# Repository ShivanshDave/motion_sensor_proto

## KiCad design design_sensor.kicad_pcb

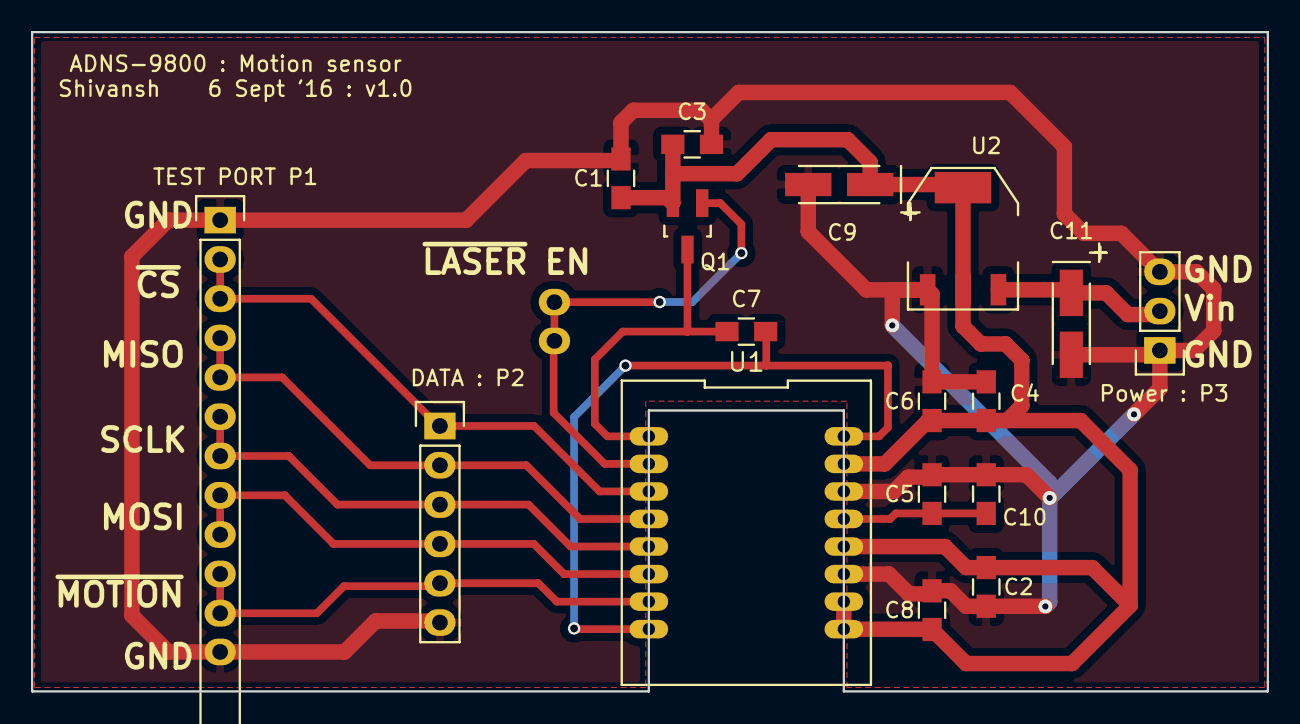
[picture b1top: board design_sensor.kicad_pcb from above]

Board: 2 copper layers, 79.8 x 42.6 mm, 17 parts (0 on the bottom side), 12 nets.

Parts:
C1: 1uF; C_0805_HandSoldering
C2, C3, C4, C10: 0.1uF; C_0805_HandSoldering
C5, C8: 10uF; C_0805_HandSoldering
C6: 3.3uF; C_0805_HandSoldering
C7: 470pF; C_0805_HandSoldering
C9, C11: 10u; TantalC_SizeA_EIA-3216_HandSoldering
DATA : P2: Data; Pin_Header_Straight_1x06
Power : P3: POWER; Pin_Header_Straight_1x03
Q1: Q_PMOS_GSD; SOT-23_Handsoldering
TEST PORT P1: Test Port; Pin_Header_Straight_1x14
U1: ADSN9800; DIP-16_SEPT2_new
U2: LD1117S33CTR; SOT-223

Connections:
/MISO: DATA : P2.2, TEST PORT P1.4, TEST PORT P1.5, U1.4
/MOSI: DATA : P2.4, TEST PORT P1.8, TEST PORT P1.9, U1.6
/SCLK: DATA : P2.3, TEST PORT P1.6, TEST PORT P1.7, U1.5
/VIN: C11.1, Power : P3.2, U2.3
/~CS: DATA : P2.1, TEST PORT P1.2, TEST PORT P1.3, U1.3
/~Laser_EN: Q1.1, TEST PORT P1.12, TEST PORT P1.13, U1.2
/~Motion: DATA : P2.5, TEST PORT P1.10, TEST PORT P1.11, U1.7
GND: C1.2, C2.2, C3.2, C4.2, C5.2, C6.2, C8.2, C9.2, C10.2, C11.2, DATA : P2.6, Power : P3.1, Power : P3.3, TEST PORT P1.1, TEST PORT P1.14, U1.11, U1.14, U2.1
unnamed: C7.1, Q1.3, U1.1
unnamed: C7.2, U1.8, U1.16
unnamed: C5.1, C10.1, U1.13
VDD: C1.1, C2.1, C3.1, C4.1, C6.1, C8.1, C9.1, Q1.2, U1.9, U1.10, U1.12, U1.15, U2.2

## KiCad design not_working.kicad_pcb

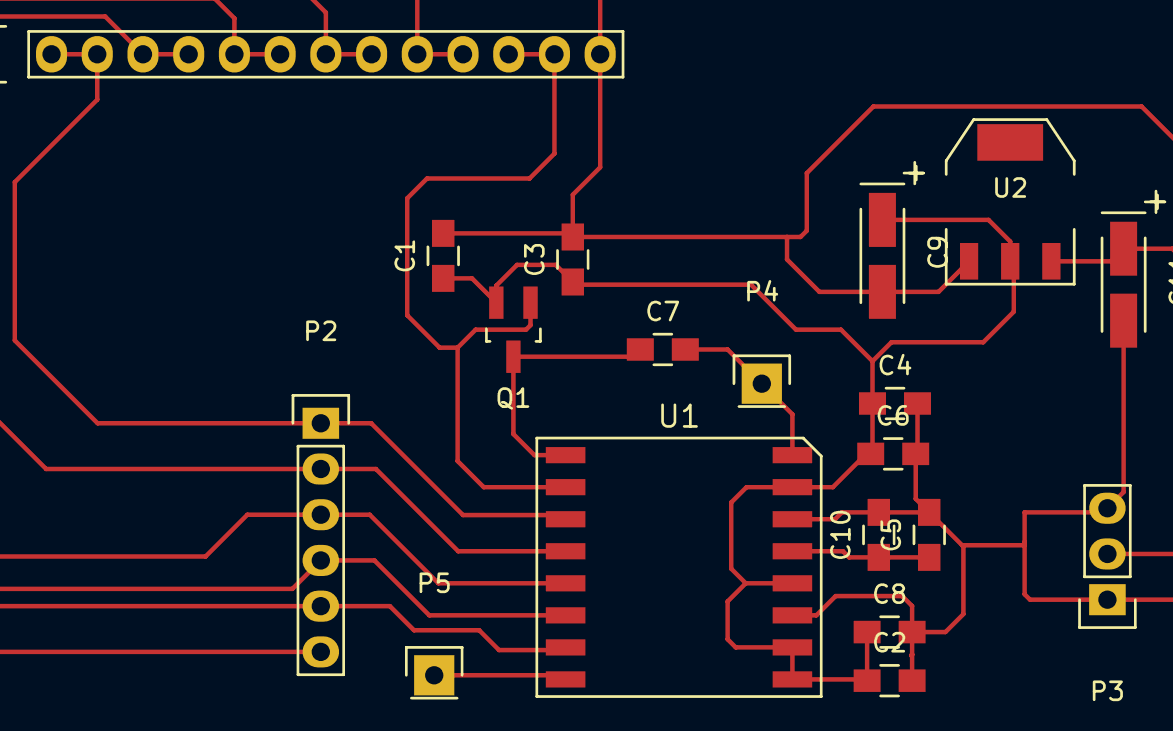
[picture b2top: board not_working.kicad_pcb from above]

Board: 2 copper layers, 19 parts (0 on the bottom side), 13 nets.

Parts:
C1: 1uF; C_0805_HandSoldering
C2, C3, C4, C10: 0.1uF; C_0805_HandSoldering
C5, C8: 10uF; C_0805_HandSoldering
C6: 3.3uF; C_0805_HandSoldering
C7: 470pF; C_0805_HandSoldering
C9, C11: 10u; TantalC_SizeA_EIA-3216_HandSoldering
P1: Test Port; Pin_Header_Straight_1x14
P2: Data; Pin_Header_Straight_1x06
P3: POWER; Pin_Header_Straight_1x03
P4: To pin 16; Pin_Header_Straight_1x01
P5: To Pin 8; Pin_Header_Straight_1x01
Q1: Q_PMOS_GSD; SOT-23_Handsoldering
U1: ADSN9800; SOIC-16_OPT_SENS
U2: LD1117S33CTR; SOT-223

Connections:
/MISO: P1.4, P1.5, P2.2, U1.4
/MOSI: P1.8, P1.9, P2.4, U1.6
/SCLK: P1.6, P1.7, P2.3, U1.5
/VIN: C11.1, P3.2, U2.3
/~CS: P1.2, P1.3, P2.1, U1.3
/~Laser_EN: P1.12, P1.13, Q1.1, U1.2
/~Motion: P1.10, P1.11, P2.5, U1.7
GND: C1.2, C2.2, C3.2, C4.2, C5.2, C6.2, C8.2, C9.2, C10.2, C11.2, P1.14, P2.6, P3.1, P3.3, U1.11, U1.14, U2.1
unnamed: C7.1, Q1.3, U1.1
unnamed: C7.2, P4.1, U1.16
unnamed: C5.1, C10.1, U1.13
unnamed: P5.1, U1.8
VDD: C1.1, C2.1, C3.1, C4.1, C6.1, C8.1, C9.1, Q1.2, U1.9, U1.10, U1.12, U1.15, U2.2

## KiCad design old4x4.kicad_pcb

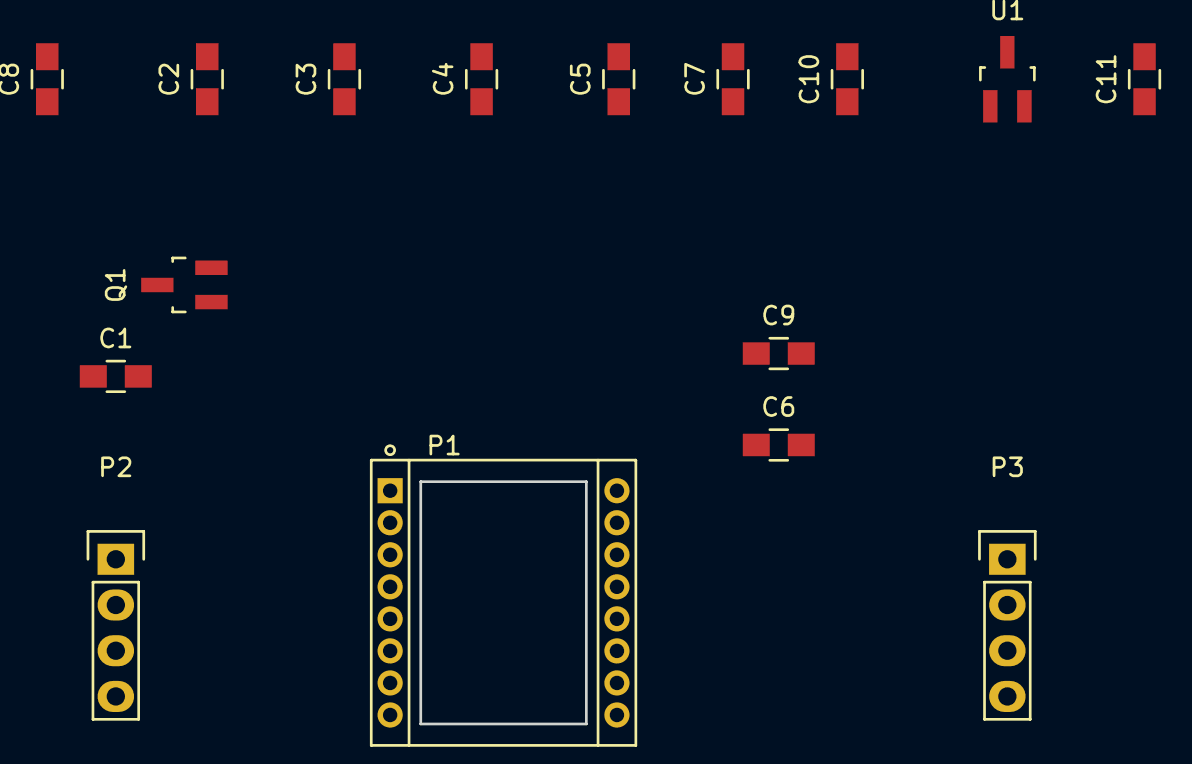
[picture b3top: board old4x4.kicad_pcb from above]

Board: 2 copper layers, 16 parts (0 on the bottom side), 13 nets, no tracks yet.

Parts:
C1: 470pF; C_0805_HandSoldering
C2, C5, C6, C7: 0.1uF; C_0805_HandSoldering
C3, C10, C11: 1uF; C_0805_HandSoldering
C4, C9: 10uF; C_0805_HandSoldering
C8: 3.3uF; C_0805_HandSoldering
P1: DIL16; Mousesensor_ADNS-9800
P2: CONN_4_L; Pin_Header_Straight_1x04
P3: CONN_4_R; Pin_Header_Straight_1x04
Q1: Q_PMOS_GSD; SOT-23_Handsoldering
U1: MCP1700T; SOT-23_Handsoldering

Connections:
AGND: C2.2, C3.2, C4.2, C5.2, C7.2, C8.2, C10.2, C11.2, P1.11, P3.2, U1.3
DGND: C6.2, C9.2, P1.14, P3.1
LSR_NEN: P1.2, Q1.1
MISO: P1.4, P2.2
MOSI: P1.6, P2.4
MOTION: P1.7, P3.4
unnamed: C1.1, P1.8, P1.16
unnamed: C1.2, P1.1, Q1.3
REFA: C6.1, C9.1, P1.13
SCLK: P1.5, P2.3
SS: P1.3, P2.1
VIN: C11.1, P3.3, U1.2
VREG: C2.1, C3.1, C4.1, C5.1, C7.1, C8.1, C10.1, P1.9, P1.10, P1.12, P1.15, Q1.2, U1.1

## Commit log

2016-09-06 :tada: Added .gitattributes
2016-09-06 Proto
    init
